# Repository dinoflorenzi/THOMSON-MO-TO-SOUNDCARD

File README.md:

# PC128 OLIVETTI PRODEST - THOMSON MO/TO SOUNDCARD

# Attention, YM2413 sound card project is still in the prototype state.
# Only the previous versions made have been tested only on PC 128 OLIVETTI PRODEST.
# The last versions with minimal changes and corrections are under test.
# Otherwise, there is an all-in-one version, developed and built by Sebastien that fully works (https://github.com/Sebastus1976/Amadeus).

## PROJECT OVERVIEW
This is a project is born to build a secondary sound card expansion for my PC 128 OLIVETTI PRODEST HOME COMPUTER.<br/>
I have designed and built two different sound cards based on two different sound chip.<br/>
One sound card is based on PSG SN76489AN sound chip, the second is based on OPLL YM2413 sound chip.<br/>
Also i have coded the ASM 6809 routines to play sound demos.<br/>

## HOW IT STARTED
Thomson computers have sound generator simply based on 6bit dac that fully commits the cpu countinuosly updating the sound samples. During sound streaming the computer can't do anything else.<br/>
Beucause of that there was the need to develop a secondary sound card based on specific sound chip that generates sound by itself, only programming your own registers.<br/>
## START POINT
Thomson computers have an expansion port with the main computer signals, data bus, address bus, chip select, master clock, and analog sound input that is mixed with the main sound generator.<br/>
<br/>
## SOUND CHIP SELECTION CRITERION
The SN76489AN first chip selection is based on its simple architecture, 8 bit bus, four channels, up to two write sequences to generates sound or noise.<br/>
The YM2413 second chip selection is also based on its simple architecture, 8 bit bus, nine channels, two write addresses to generates sound with hardware instruments and rythems.<br/>
Single board develepments are better described to the links below or wiki section<br/>
[SN76489AN SOUND CARD DEVELOPMENT](https://github.com/dinoflorenzi/THOMSON-MO-TO-SOUNDCARD/wiki/SN76489AN-MOTO-SOUND-CARD)<br/>
[YM2413 SOUND CARD DEVELOPMENT](https://github.com/dinoflorenzi/THOMSON-MO-TO-SOUNDCARD/wiki/YM2413-MOTO-SOUND-CARD)<br/>
## CONTEMPORARY USAGE
By properly setting card jumpers it changes the address. In this way you can mount two sound cards working  simultaneously.<br/>
The interconnection card is a third-party project.<br/>
The assembly of the cards in this photo is the precious contribution of Benoit Rousseau. He help me to debug the cards on Thomson TO target.<br/>

<br/>
## SOFTWARE TOOLS
[Kicad](https://www.kicad.org/) and [Freerounting](https://freerouting.org/) to develop schematics and pcb.<br/>
DCMOTO emulator fully emulates both sound cards (http://dcmoto.free.fr/emulateur/index.html)<br/>
## RESOURCES
https://en.wikipedia.org/wiki/Texas_Instruments_SN76489<br/>
https://en.wikipedia.org/wiki/Yamaha_YM2413<br/>
http://dcmoto.free.fr/<br/>
https://vgmrips.net/packs/<br/>
https://www.smspower.org/Music/VGMs<br/>
http://atjs.mbnet.fi/mc6809/<br/>
http://map.grauw.nl/resources/sound/texas_instruments_sn76489an.pdf<br/>
http://map.grauw.nl/resources/sound/yamaha_ym2413_ds.pdf<br/>

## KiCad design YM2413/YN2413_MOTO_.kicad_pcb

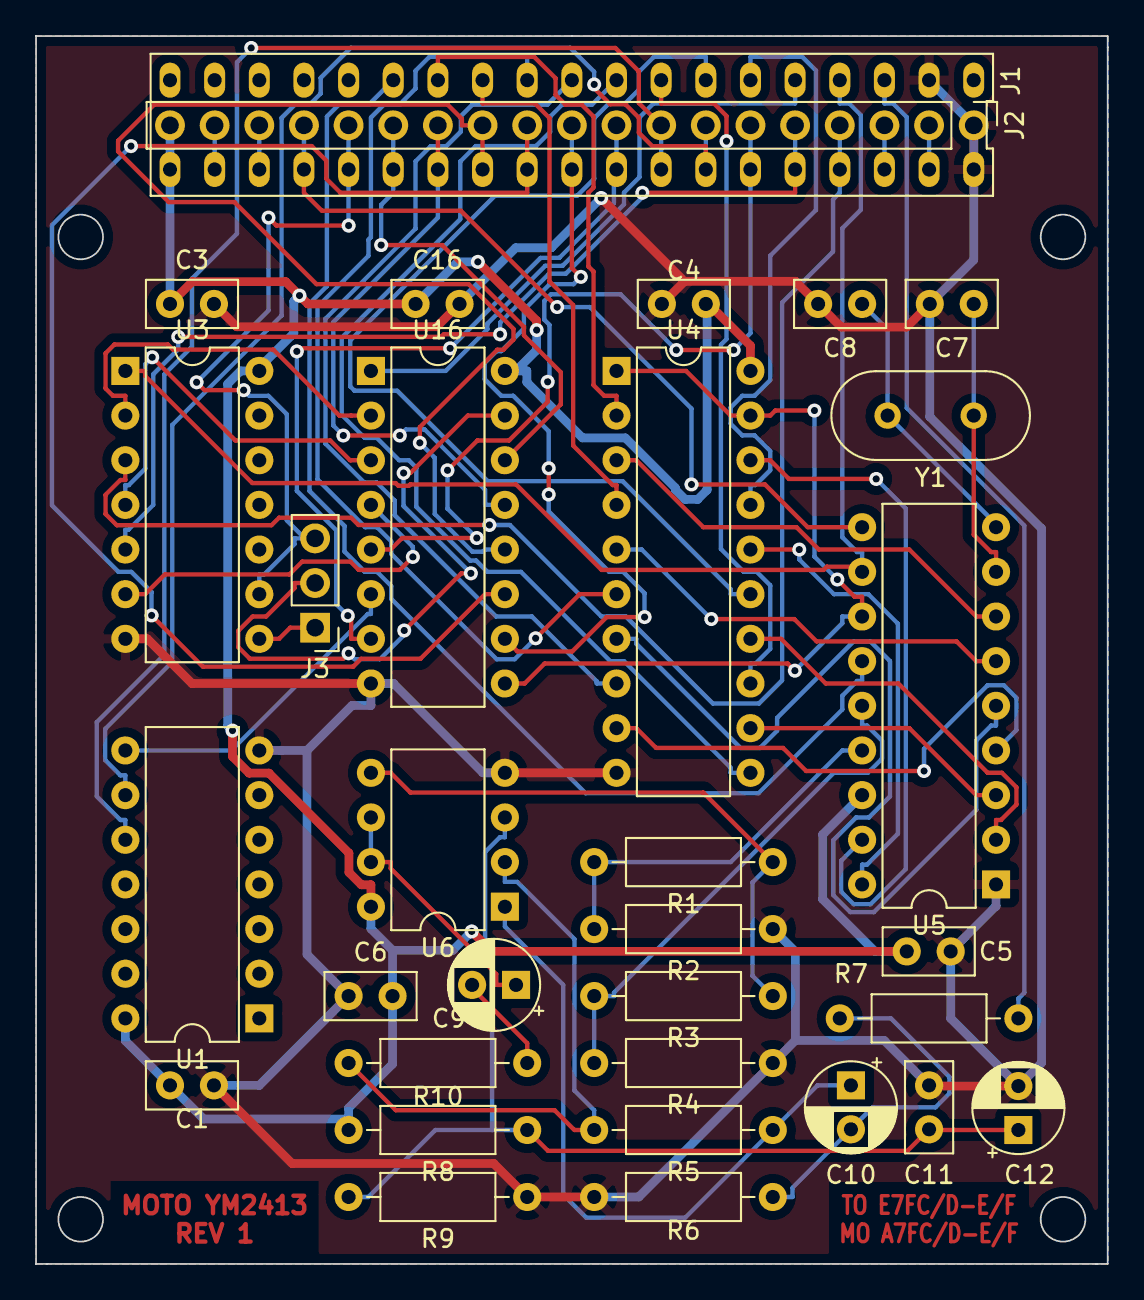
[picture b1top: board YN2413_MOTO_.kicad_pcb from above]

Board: 2 copper layers, 61.0 x 69.8 mm, 32 parts (0 on the bottom side), 57 nets.

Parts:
C1, C3, C4, C5, C6, C11, C16: 100nF; C_Disc_D5.0mm_W2.5mm_P2.50mm
C7, C8: 27pF; C_Disc_D5.0mm_W2.5mm_P2.50mm
C9, C12: 1uF; CP_Radial_D5.0mm_P2.50mm
C10: 10uF; CP_Radial_D5.0mm_P2.50mm
J1: Conn_02x19_Row_Letter_Last; DIP-38_Edge_Connector
J2: Conn_01x19; PinHeader_1x19_P2.54mm_Vertical
J3: Conn_01x03_Male; PinHeader_1x03_P2.54mm_Vertical
R1, R3: 4700; R_Axial_DIN0207_L6.3mm_D2.5mm_P10.16mm_Horizontal
R2, R4: 2200; R_Axial_DIN0207_L6.3mm_D2.5mm_P10.16mm_Horizontal
R5: 100K; R_Axial_DIN0207_L6.3mm_D2.5mm_P10.16mm_Horizontal
R6, R7, R8, R9: 1000; R_Axial_DIN0207_L6.3mm_D2.5mm_P10.16mm_Horizontal
R10: 10K; R_Axial_DIN0207_L6.3mm_D2.5mm_P10.16mm_Horizontal
U1: 74LS08; DIP-14_W7.62mm
U3: 74LS04; DIP-14_W7.62mm
U4: 74LS244; DIP-20_W7.62mm
U5: YM2413; DIP-18_W7.62mm
U6: TL072; DIP-8_W7.62mm
U16: 74LS133; DIP-16_W7.62mm
Y1: 3.576 MHz; Crystal_HC18-U_Vertical

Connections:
+5V: C1.1, C3.1, C4.1, C5.1, C6.2, C16.1, J1.19a, J2.19, R8.2, U1.14, U3.14, U4.20, U5.16, U6.8, U16.16
/A1: J1.15a, J2.15, J3.3, U3.9
/A2: J1.14a, J2.14, U16.14
/A3: J1.13a, J2.13, U16.13
/A4: J1.12a, J2.12, U16.12
/A5: J1.11a, J2.11, U16.11
/A6: J1.10a, J2.10, U16.10
/A7: J1.9a, J2.9, U16.7
/A8: J1.8a, J2.8, U1.10
/A9: J1.7a, J2.7, U1.9
/A10: J1.6a, J2.6, U16.5
/A11: J1.5a, J2.5, U3.5
/D0: J1.13b, U4.2
/D1: J1.12b, U4.4
/D2: J1.11b, U4.6
/D3: J1.10b, U4.8
/D4: J1.9b, U4.11
/D5: J1.8b, U4.13
/D6: J1.7b, U4.15
/D7: J1.6b, U4.17
/E: J1.5b, U16.1
/SON: J1.3b, R7.2
/\A7XX: J1.3a, J2.3
/\AXXX: J1.4a, J2.4, U3.3
/\CLRG: J1.2a, J2.2
A0: J1.16a, J2.16, U5.10
GND: C1.2, C3.2, C4.2, C5.2, C6.1, C7.2, C8.2, C11.1, C12.2, C16.2, J1.1a, J1.2b, J2.1, R2.1, R4.1, R6.1, R9.1, U1.7, U3.7, U4.10, U5.1, U6.4, U16.8
unnamed: C7.1, U5.8, Y1.1
unnamed: C8.1, U5.9, Y1.2
unnamed: C9.1, U6.6, U6.7
unnamed: C9.2, R10.2
unnamed: C10.1, R5.1, U6.1
unnamed: C10.2, R6.2, R7.1
unnamed: C11.2, C12.1, R8.1, R9.2, U6.3
unnamed: J1.17a, J2.17
unnamed: J1.18a, J2.18
unnamed: J3.1, U3.8
unnamed: J3.2, U16.15
unnamed: R1.1, R3.1, U6.5
unnamed: R1.2, R2.2, U5.15
unnamed: R3.2, R4.2, U5.14
unnamed: R5.2, R10.1, U6.2
unnamed: U1.8, U16.6
unnamed: U4.3, U5.7
unnamed: U4.5, U5.6
unnamed: U4.7, U5.5
unnamed: U4.9, U5.4
unnamed: U4.12, U5.3
unnamed: U4.14, U5.2
unnamed: U4.16, U5.18
unnamed: U4.18, U5.17
unnamed: U3.2, U16.2
unnamed: U3.4, U16.3
unnamed: U3.6, U16.4
unnamed: U4.1, U4.19, U5.12, U16.9
RESET: J1.14b, U5.13
RW: J1.4b, U3.1, U5.11

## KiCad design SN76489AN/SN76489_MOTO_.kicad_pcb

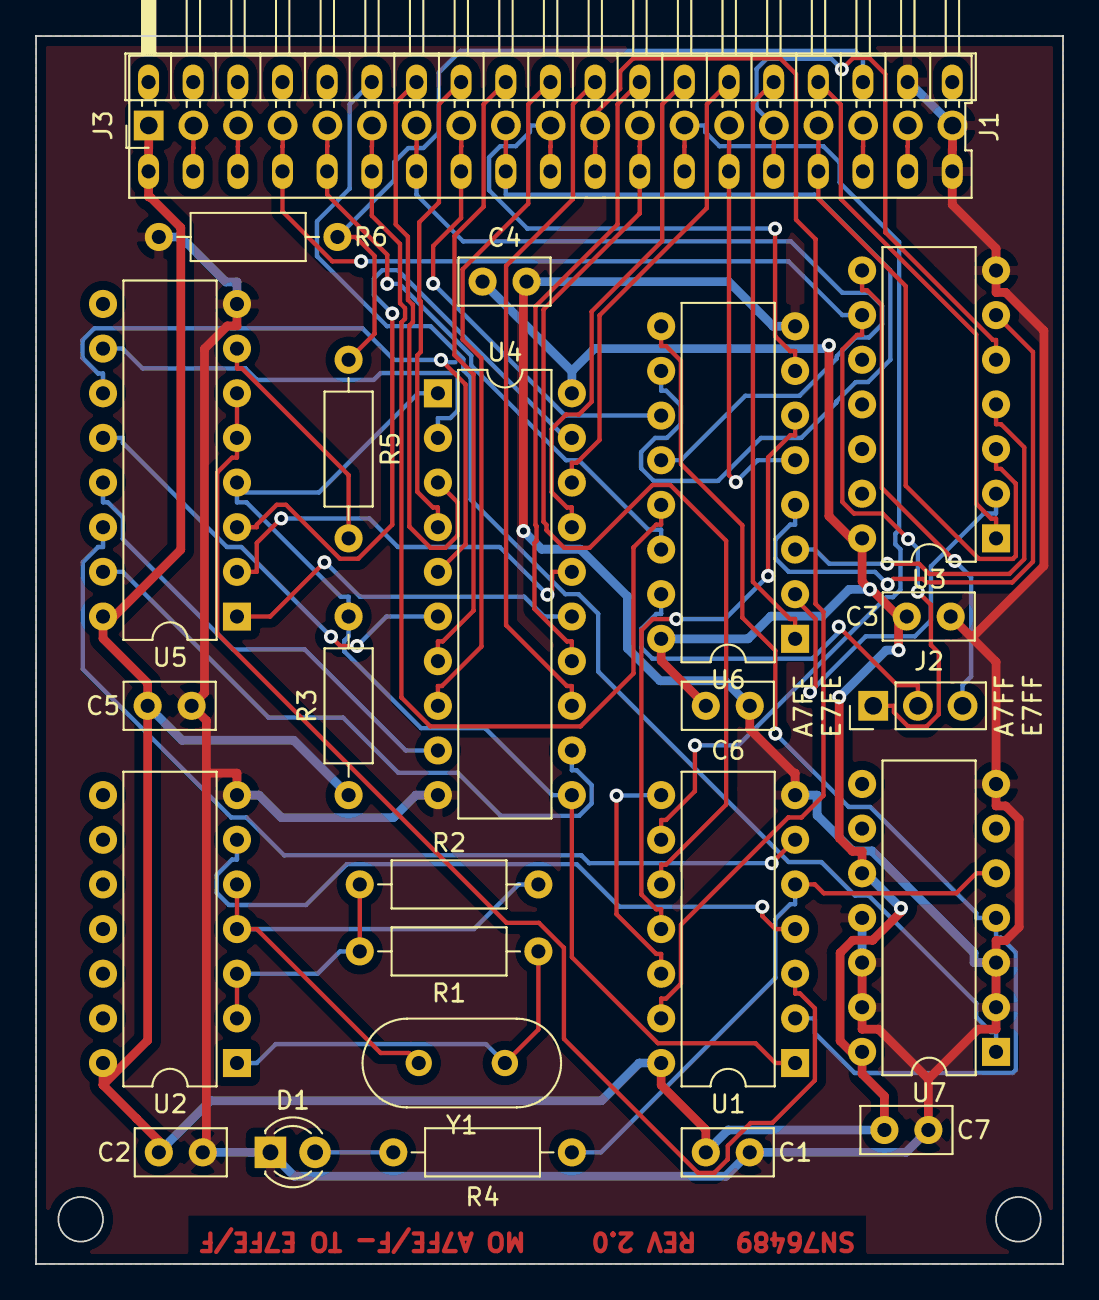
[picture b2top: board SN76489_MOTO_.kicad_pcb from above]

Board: 2 copper layers, 58.4 x 69.8 mm, 25 parts (0 on the bottom side), 57 nets.

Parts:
C1, C2, C3, C4, C5, C6, C7: 100nF; C_Disc_D5.0mm_W2.5mm_P2.50mm
D1: LED; LED_D3.0mm
J1: Conn_02x19_Row_Letter_Last; DIP-38_Edge_Connector
J2: Conn_01x03_Male; PinHeader_1x03_P2.54mm_Vertical
J3: Conn_01x19; PinHeader_1x19_P2.54mm_Horizontal
R1, R2, R3: 2000; R_Axial_DIN0207_L6.3mm_D2.5mm_P10.16mm_Horizontal
R4: 250; R_Axial_DIN0207_L6.3mm_D2.5mm_P10.16mm_Horizontal
R5, R6: 1000; R_Axial_DIN0207_L6.3mm_D2.5mm_P10.16mm_Horizontal
U1: 74LS08; DIP-14_W7.62mm
U2, U3: 74LS04; DIP-14_W7.62mm
U4: 74LS373; DIP-20_W7.62mm
U5: SN76489AN; DIP-16_W7.62mm
U6: 74LS133; DIP-16_W7.62mm
U7: 74LS74; DIP-14_W7.62mm
Y1: 3.576 MHz; Crystal_HC18-U_Vertical

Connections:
+5V: C1.1, C2.1, C3.1, C4.1, C5.1, C6.1, C7.1, J1.19a, J3.1, R3.1, U1.14, U2.14, U3.14, U4.20, U5.16, U6.16, U7.10, U7.14
/A0: J1.16a, J2.1, J3.4, U3.9
/A1: J1.15a, J3.5, U6.14
/A2: J1.14a, J3.6, U6.13
/A3: J1.13a, J3.7, U6.12
/A4: J1.12a, J3.8, U6.11
/A5: J1.11a, J3.9, U6.10
/A6: J1.10a, J3.10, U6.7
/A7: J1.9a, J3.11, U1.13
/A8: J1.8a, J3.12, U1.10
/A9: J1.7a, J3.13, U1.9
/A10: J1.6a, J3.14, U6.5
/A11: J1.5a, J3.15, U3.5
/D0: J1.13b, U4.3
/D1: J1.12b, U4.4
/D2: J1.11b, U4.7
/D3: J1.10b, U4.8
/D4: J1.9b, U4.13
/D5: J1.8b, U4.14
/D6: J1.7b, U4.17
/D7: J1.6b, U4.18
/E: J1.5b, U6.1
/LT1: R3.2, U1.1, U4.1, U4.11, U5.4
/RW: J1.4b, U3.1
/SON: J1.3b, R5.1, R6.1
/\EXXX: J1.4a, J3.16, U3.3
/\RESET: J1.14b, U7.1
GND: C1.2, C2.2, C3.2, C4.2, C5.2, C6.2, C7.2, D1.1, J1.1a, J1.2b, J3.19, R6.2, U1.7, U2.7, U3.7, U4.10, U5.8, U6.8, U7.2, U7.3, U7.7, U7.11, U7.12, U7.13
unnamed: D1.2, R4.1
unnamed: J1.2a, J3.18
unnamed: J1.3a, J3.17
unnamed: J1.17a, J3.3
unnamed: J1.18a, J3.2
unnamed: J2.2, U6.15
unnamed: J2.3, U3.8
unnamed: R1.1, U2.1, Y1.1
unnamed: R1.2, R2.1, U2.2, U2.3
unnamed: R2.2, U2.4, U2.5, Y1.2
unnamed: R4.2, U1.5, U7.5
unnamed: R5.2, U5.7
unnamed: U1.2, U6.9, U7.4
unnamed: U1.3, U5.5, U5.6
unnamed: U1.4, U2.6
unnamed: U1.6, U5.14
unnamed: U1.11, U6.6
unnamed: U1.8, U1.12
unnamed: U3.2, U6.2
unnamed: U3.4, U6.3
unnamed: U3.6, U6.4
unnamed: U4.2, U5.10
unnamed: U4.5, U5.11
unnamed: U4.6, U5.12
unnamed: U4.9, U5.13
unnamed: U4.12, U5.15
unnamed: U4.15, U5.1
unnamed: U4.16, U5.2
unnamed: U4.19, U5.3

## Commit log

2023-01-23 Add files via upload
    Version modified by Sebastien to improve sound quality.
